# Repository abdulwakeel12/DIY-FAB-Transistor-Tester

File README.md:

# DIY FAB Transistor Tester

> **4th Semester Project**  
> **Duration:** March 2022 – July 2022  
> **Institution:** Sukkur IBA University  
> **Department:** Electrical Engineering  
> **Course:** Introduction to Embedded System  
> **Supervisor:** Dr. Muhammad Asim Samejo   

---

## 👥 Group Members

- Wakeel Ahmed (CMS ID: 033-19-0026)  
- Bhai Khan (CMS ID: 033-19-0015)

---

## 📌 Project Description

This DIY FAB Transistor Tester is a compact device designed to identify and measure various electronic components. It uses an ATmega328P-based Arduino UNO to test and display data such as pin configuration, polarity, and key parameters on a 16x2 LCD screen.

It supports automatic identification of:
- Bipolar Junction Transistors (NPN, PNP)
- MOSFETs (N-Channel, P-Channel)
- JFETs, IGBTs, Thyristors, and Triacs
- Diodes and Zener Diodes
- Capacitors and Resistors

---

## 🧰 Technologies & Tools Used

- **Arduino UNO (ATmega328P)**
- **Eagle PCB Design Software**
- **Ultimaker 3D Printer**
- **Cura Slicer for 3D Printing**
- **HTML, CSS** (for project documentation)
- **Fritzing** (for high-level schematic design)
- **FTDI, ICSP Bootloader Programming**
- **16x2 LCD Display**

---

## 💡 Features

- Auto-detection of transistor type, pins, and characteristics
- Displays:
  - Gain (hFE), V<sub>BE</sub>
  - R<sub>DS(on)</sub> for MOSFETs
  - Capacitance and resistance
- Menu selection & self-test modes
- USB-powered via Mini USB port
- Fully enclosed in a 3D-printed custom case

---

## 📷 Project Gallery

project/
│
├── index.html # Project report
├── style.css # Styling
├── images/ # Photos, schematics, designs...

---

## 💰 Bill of Materials

| Component                  | Cost (PKR) |
|---------------------------|------------|
| Full PCB                  | Rs. 1,500   |
| LCD Display               | Rs. 488     |
| 3D Printing (Plastic)     | Rs. 2,500   |
| Steel Rod                 | Rs. 600     |
| **Total**                 | **Rs. 5,088** |

---

## 🔗 Project Resources

- 🔗 [**Reference Guide**](https://create.arduino.cc/projecthub/plouc68000/ardutester-v1-13-the-arduino-uno-transistor-tester-dbafb4)
- 💻 [**Source Code (Arduino)**](https://create.arduino.cc/editor/plouc68000/d6b548e6-37af-4cf0-b95f-cbaa9e89ea72/preview)
- 📐 [**CAD STL File**](https://github.com/wagiminator/ATmega-Transistor-Tester/blob/master/hardware/TransistorTester_case.stl)
- 🧩 [**Fritzing Circuit File**](https://fritzing.org/projects/tester)

---

## 📽️ Demonstration Videos

- [<a href="https://www.youtube.com/embed/zdPWsUJlSmU" target="_blank">📺 Breadboard Prototype & Bootloading</a>
- [<a href="https://www.youtube.com/embed/i-WZqEvgACc" target="_blank">📺 Final Circuit Operation</a>

---

## 💼 Business Objective

To design a low-cost, portable, and easy-to-use transistor tester that provides more detail than standard multimeters — including automatic schematic recognition, polarity, and gain factor measurement — making it ideal for academic labs and DIY engineers.

---

## 🧑‍🏫 Supervision

**Dr. Muhammad Asim Samejo**  
Department of Electrical Engineering  
Sukkur IBA University

---

## 🧑‍💻 Developed By

- **Wakeel Ahmed** (033-19-0026)  
- **Bhai Khan** (033-19-0015)

---

## 📜 License

This project is intended for educational purposes.  
© 2022 Bhai Khan & Wakeel Ahmed — All rights reserved.

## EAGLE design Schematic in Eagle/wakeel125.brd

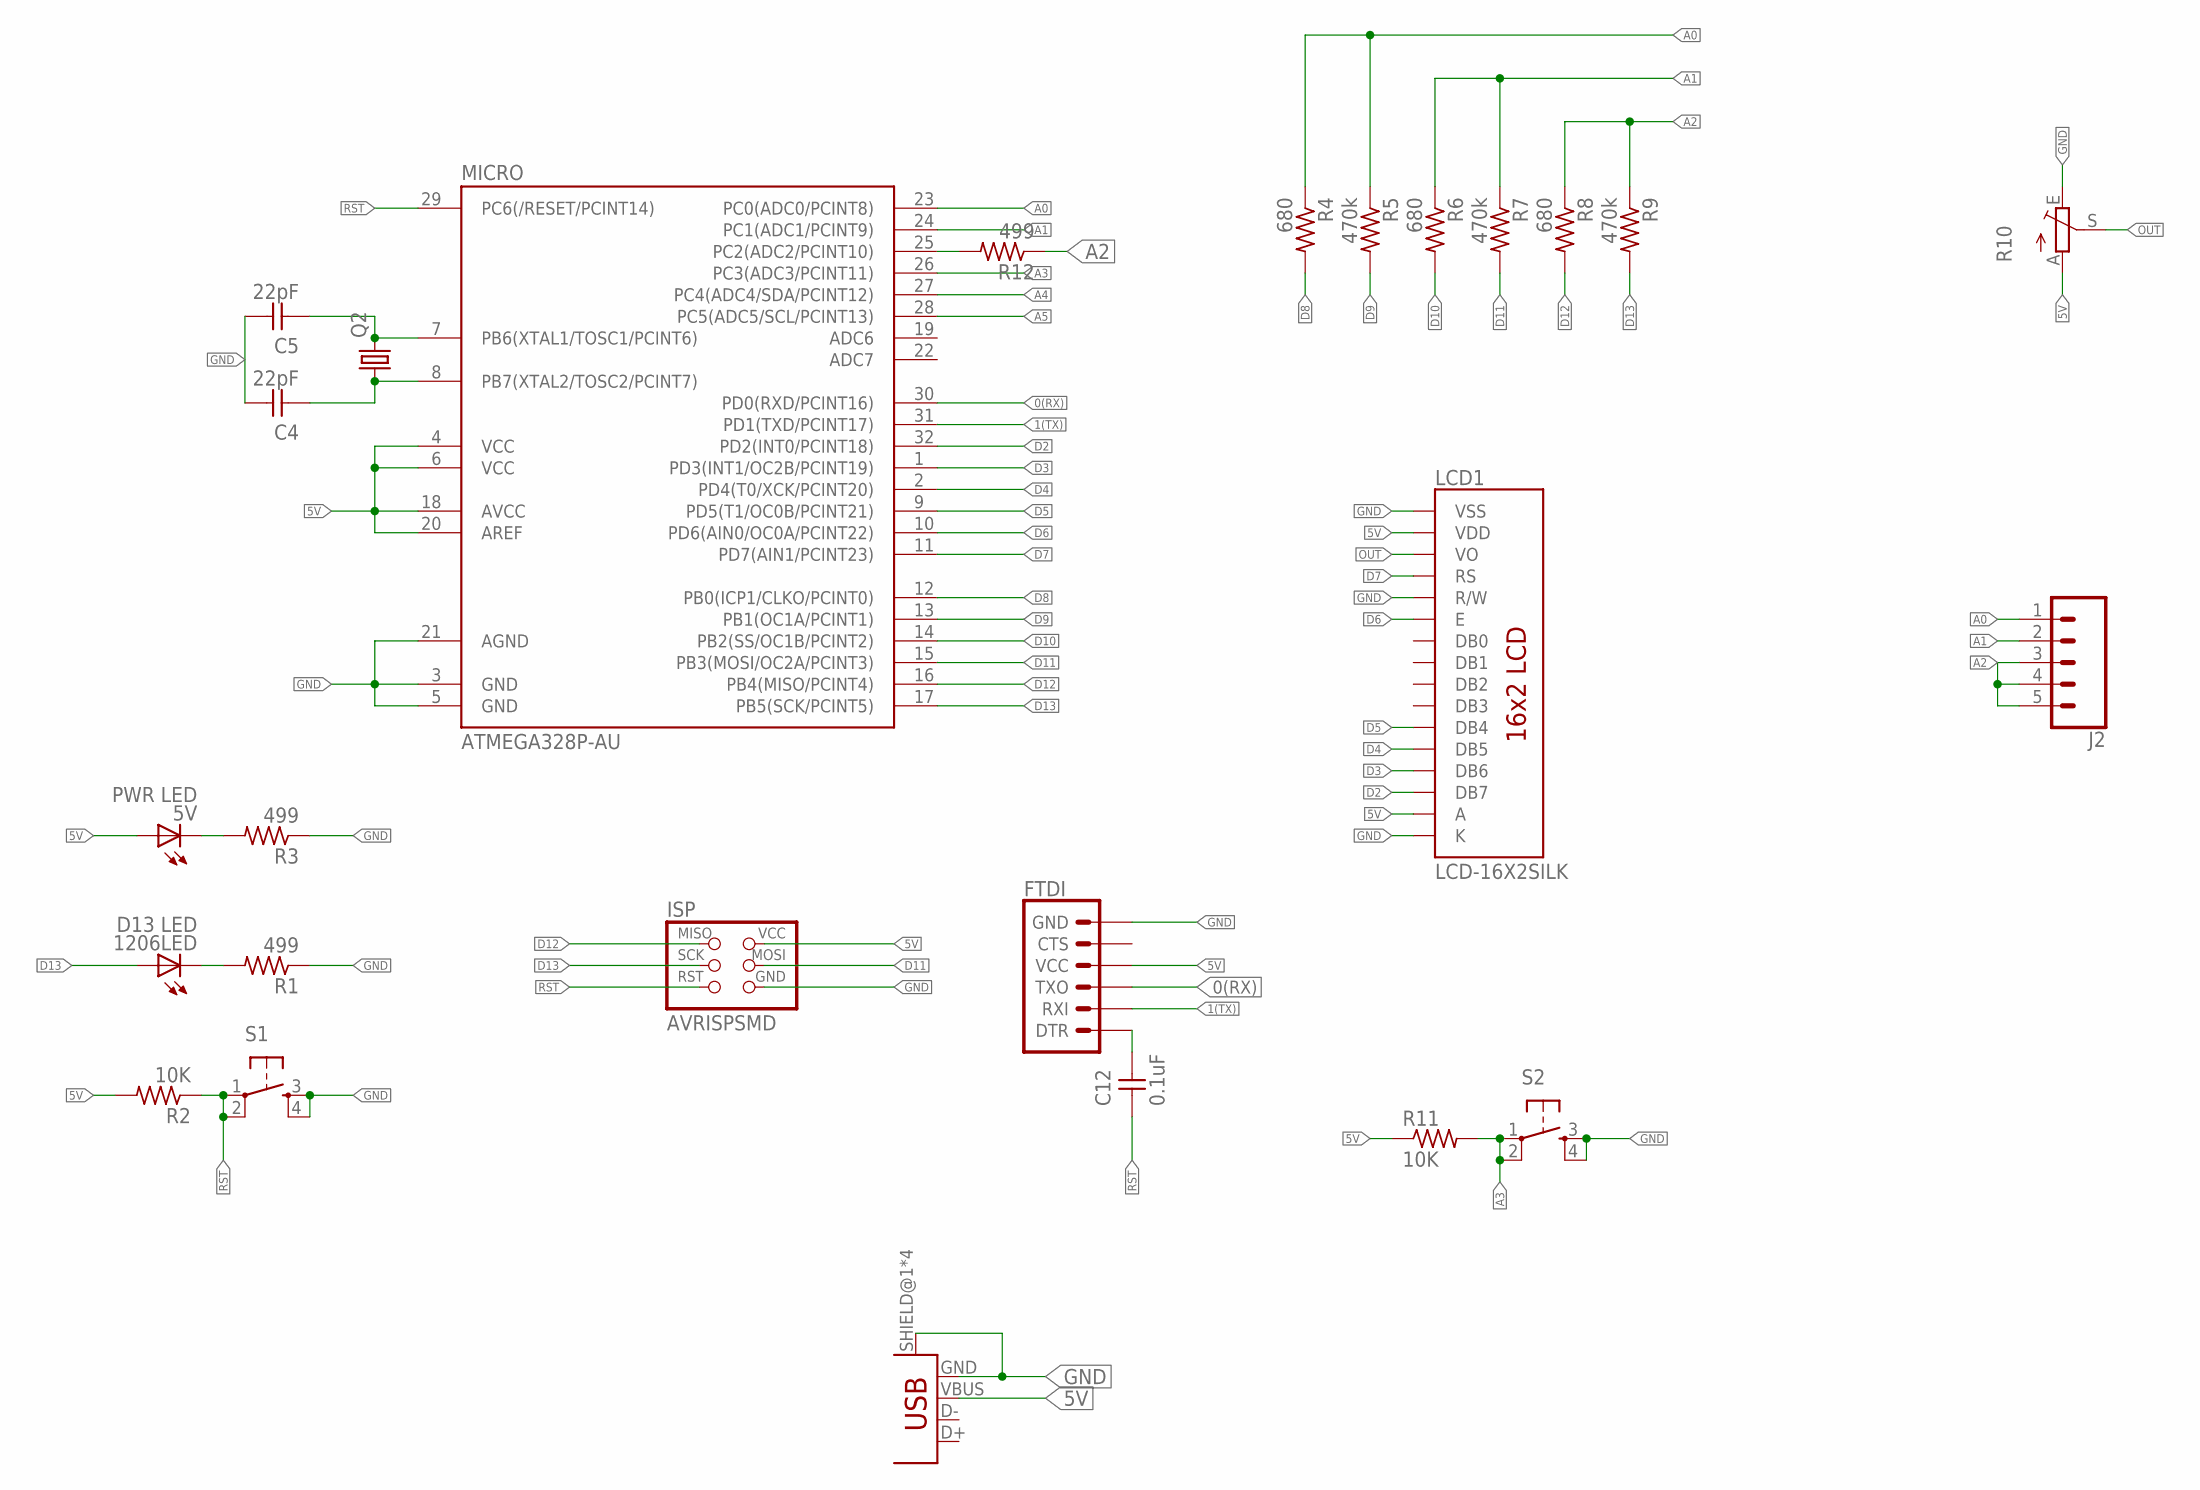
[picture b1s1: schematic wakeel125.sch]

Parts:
5V: PWR LED; LED1206FAB
1206LED: D13 LED; LED1206FAB
C4, C5: 22pF; C1206FAB
C12: 0.1uF; C1206FAB
CN1: USB_MINIB
FTDI: 6_PIN_SERIAL_TARGET_SILK; 1X06
ISP: AVRISPSMD; 2X03SMD
J2: CONN_05; 1X05
LCD1: LCD-16X2SILK; LCD-16X2
MICRO: ATMEGA328P-AU; TQFP32-08
Q2: CRYSTALHC49U70; HC49U70
R1, R3, R12: 499; R1206FAB
R2, R11: 10K; R1206FAB
R4, R6, R8: 680; R1206FAB
R5, R7, R9: 470k; R1206FAB
R10: TRIM_EU-B64W; B64W
S1, S2: 6MM_SWITCH6MM_SWITCH; 6MM_SWITCH

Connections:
0(RX): FTDI.3 (TXO), MICRO.30 (PD0(RXD/PCINT16))
1(TX): FTDI.2 (RXI), MICRO.31 (PD1(TXD/PCINT17))
5V: 5V.1 (A), CN1.VBUS, FTDI.4 (VCC), ISP.2 (VCC), LCD1.2 (VDD), LCD1.15 (A), MICRO.4 (VCC), MICRO.6 (VCC), MICRO.18 (AVCC), MICRO.20 (AREF), R2.2, R10.A, R11.1
A0: J2.1, MICRO.23 (PC0(ADC0/PCINT8)), R4.1, R5.1
A1: J2.2, MICRO.24 (PC1(ADC1/PCINT9)), R6.1, R7.1
A2: J2.3, J2.4, J2.5, R8.1, R9.1, R12.1
A3: MICRO.26 (PC3(ADC3/PCINT11)), R11.2, S2.1, S2.2 (P1)
A4: MICRO.27 (PC4(ADC4/SDA/PCINT12))
A5: MICRO.28 (PC5(ADC5/SCL/PCINT13))
D2: LCD1.14 (DB7), MICRO.32 (PD2(INT0/PCINT18))
D3: LCD1.13 (DB6), MICRO.1 (PD3(INT1/OC2B/PCINT19))
D4: LCD1.12 (DB5), MICRO.2 (PD4(T0/XCK/PCINT20))
D5: LCD1.11 (DB4), MICRO.9 (PD5(T1/OC0B/PCINT21))
D6: LCD1.6 (E), MICRO.10 (PD6(AIN0/OC0A/PCINT22))
D7: LCD1.4 (RS), MICRO.11 (PD7(AIN1/PCINT23))
D8: MICRO.12 (PB0(ICP1/CLKO/PCINT0)), R4.2
D9: MICRO.13 (PB1(OC1A/PCINT1)), R5.2
D10: MICRO.14 (PB2(SS/OC1B/PCINT2)), R6.2
D11: ISP.4 (MOSI), MICRO.15 (PB3(MOSI/OC2A/PCINT3)), R7.2
D12: ISP.1 (MISO), MICRO.16 (PB4(MISO/PCINT4)), R8.2
D13: 1206LED.1 (A), ISP.3 (SCK), MICRO.17 (PB5(SCK/PCINT5)), R9.2
GND: C4.2, C5.2, CN1.GND, CN1.SHIELD@1 (SHIELD), CN1.SHIELD@2 (SHIELD), CN1.SHIELD@3 (SHIELD), CN1.SHIELD@4 (SHIELD), FTDI.6 (GND), ISP.6 (GND), LCD1.1 (VSS), LCD1.5 (R/W), LCD1.16 (K), MICRO.3 (GND), MICRO.5 (GND), MICRO.21 (AGND), R1.1, R3.1, R10.E, S1.3 (S), S1.4 (S1), S2.3 (S), S2.4 (S1)
unnamed: 1206LED.2 (C), R1.2
unnamed: 5V.2 (C), R3.2
unnamed: C5.1, MICRO.7 (PB6(XTAL1/TOSC1/PCINT6)), Q2.2
unnamed: C4.1, MICRO.8 (PB7(XTAL2/TOSC2/PCINT7)), Q2.1
unnamed: MICRO.25 (PC2(ADC2/PCINT10)), R12.2
unnamed: C12.2, FTDI.1 (DTR)
OUT: LCD1.3 (VO), R10.S
RST: C12.1, ISP.5 (RST), MICRO.29 (PC6(/RESET/PCINT14)), R2.1, S1.1, S1.2 (P1)

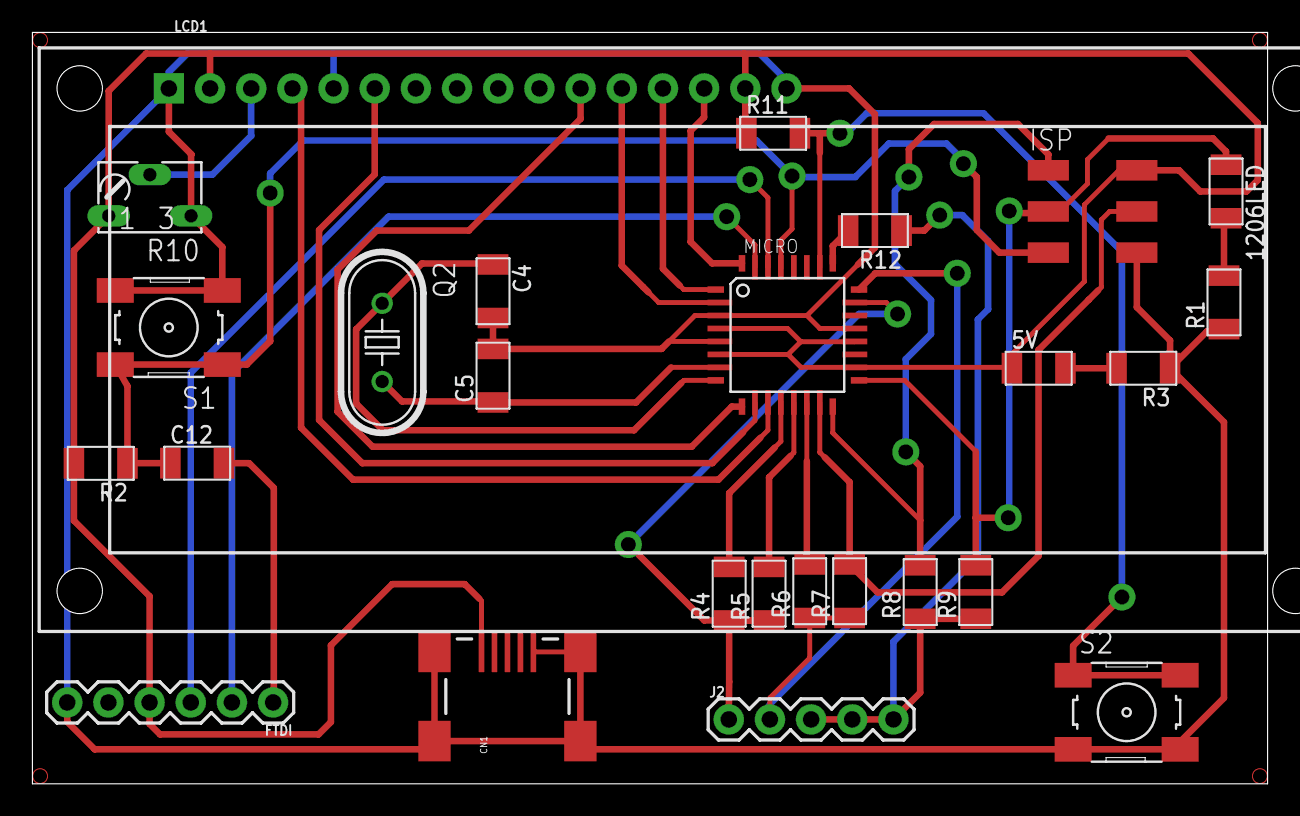
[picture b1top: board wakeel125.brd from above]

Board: 2 copper layers, 76.2 x 46.4 mm, 26 parts (0 on the bottom side), 28 nets.

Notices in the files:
parts and their libraries:
SparkFun-Connectors: Licensing: Creative Commons ShareAlike 4.0 International - https://creativecommons.org/licenses/by-sa/4.0
